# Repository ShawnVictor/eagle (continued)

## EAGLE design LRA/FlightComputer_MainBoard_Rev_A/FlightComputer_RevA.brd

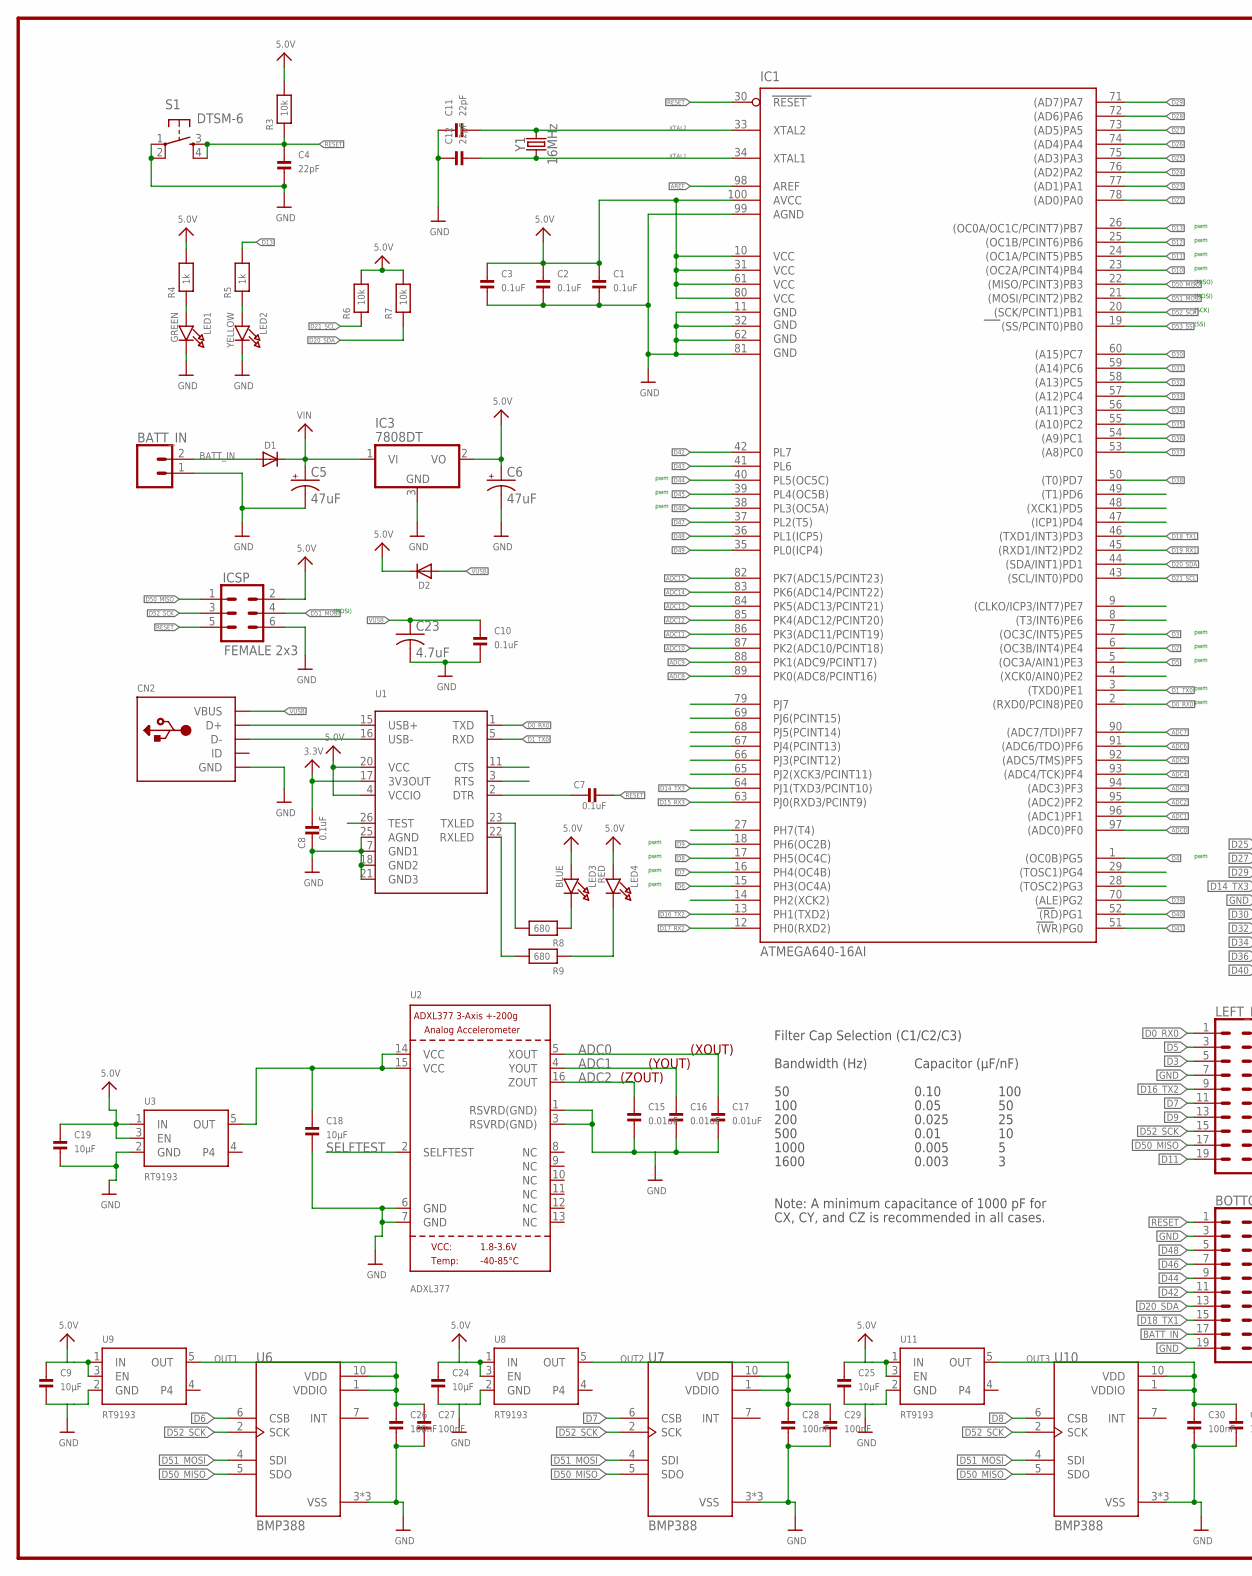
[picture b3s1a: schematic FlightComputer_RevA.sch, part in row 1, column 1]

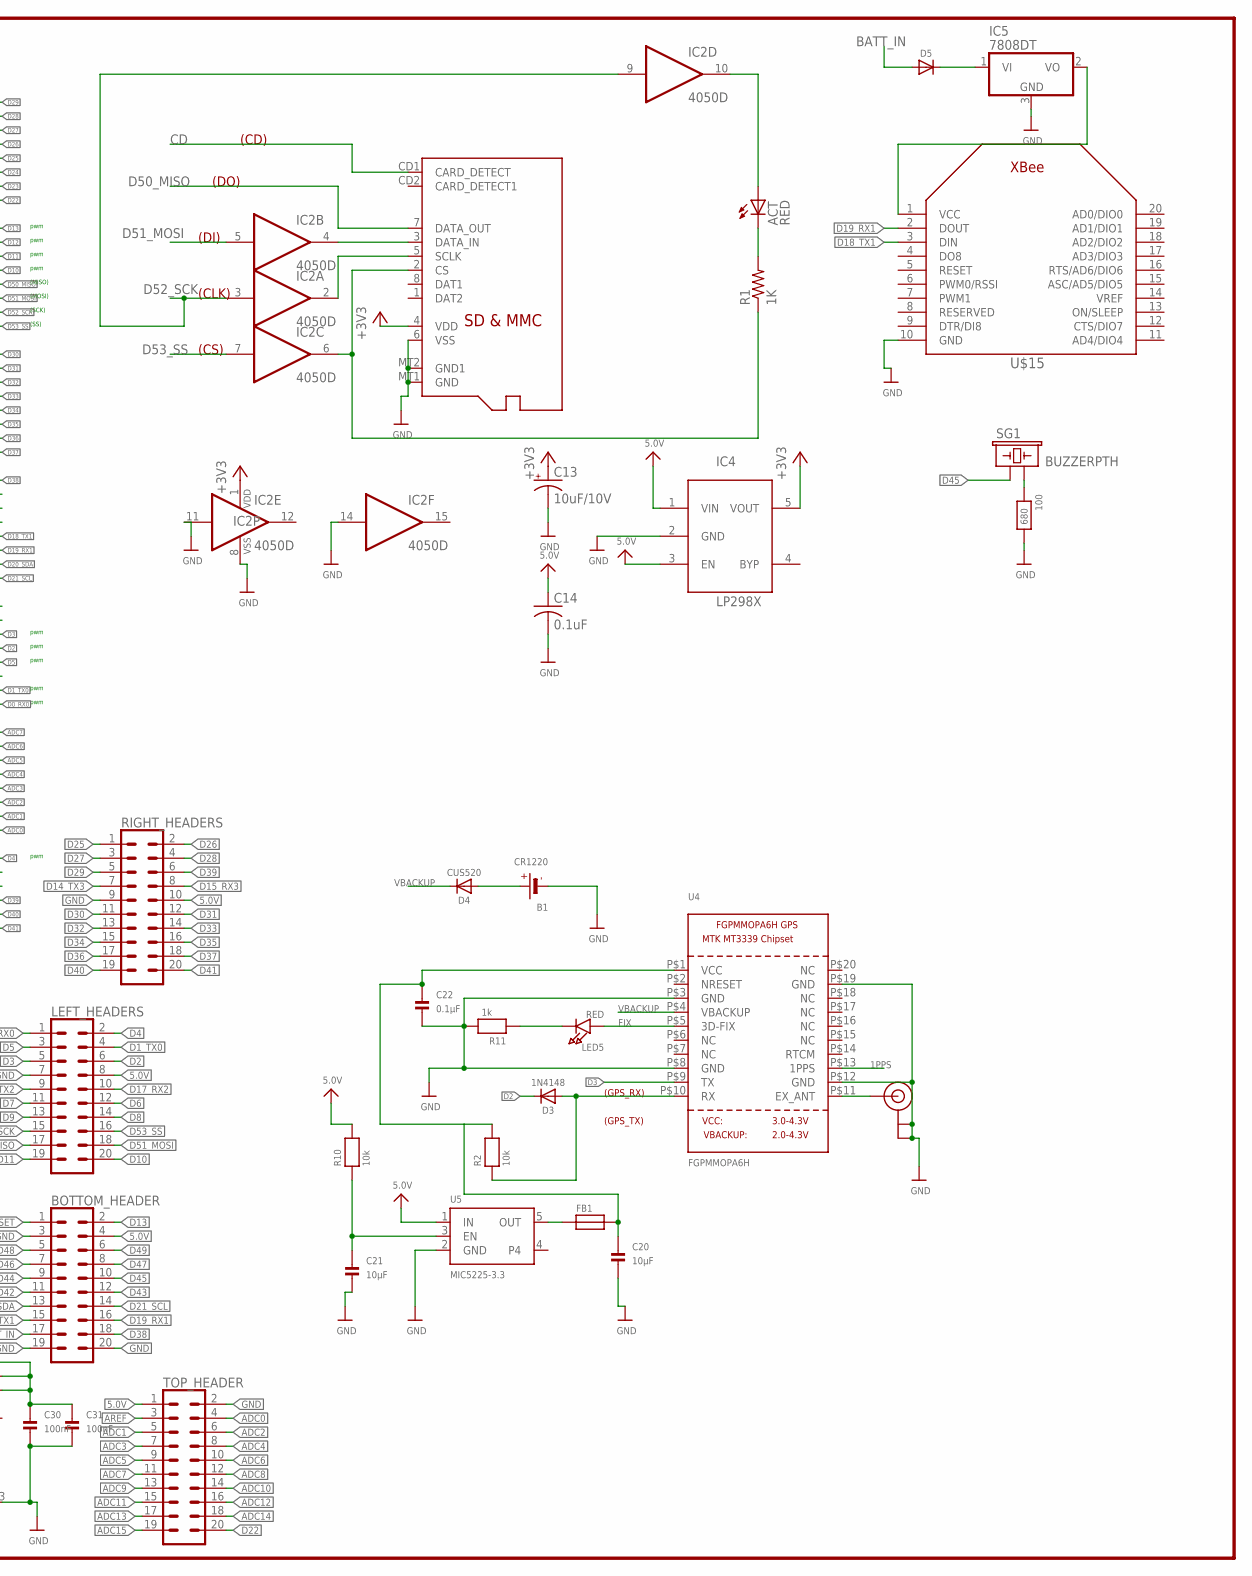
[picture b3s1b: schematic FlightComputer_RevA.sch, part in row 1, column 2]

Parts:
100: 680; 0603
ACT: RED; CHIP-LED0805
B1: CR1220
BATT_IN: CONN_02; 1X02
BOTTOM_HEADER: CONN_10X2; 2X10
C1, C2, C3, C7, C8, C10: 0.1uF; 0603
C4, C11, C12: 22pF; 0603
C5, C6: 47uF; PANASONIC_D
C9, C18, C19, C20, C21, C24, C25: 10µF; 0603
C13: 10uF/10V; A/3216-18R
C14: 0.1uF; C0805K
C15, C16, C17: 0.01uF; 0603
C22: 0.1µF; 0603
C23: 4.7uF; C0603
C26, C27, C28, C29, C30, C31: 100nF; 0603
CN2: USBMINIB; USB-MINIB
D1, D2, D5: DIODESOD-123; SOD-123
D3: 1N4148; SOD-323
D4: CUS520; SOD-323
FB1: FERRITE; 0603
IC1: ATMEGA640-16AI; TQFP100
IC2: 4050D; SO16
IC3, IC5: 7808DT; TO252
IC4: LP298XS; SOT23-5L
ICSP: FEMALE 2x3; 2X3
LED1: GREEN; CHIPLED_0603
LED2: YELLOW; CHIPLED_0603
LED3: BLUE; CHIPLED_0603
LED4: RED; CHIPLED_0603
LED5: RED; CHIPLED_0805
LEFT_HEADERS: CONN_10X2; 2X10
R1: 1K; R0805
R2, R3, R6, R7, R10: 10k; 0603
R4, R5, R11: 1k; 0603
R8, R9: 680; 0603
RIGHT_HEADERS: CONN_10X2; 2X10
S1: DTSM-6
SG1: BUZZERPTH; BUZZER-12MM
TOP_HEADER: CONN_10X2; 2X10
U1: FT232RLSSOP28; SSOP28DB
U2: ADXL377; LFCSP16_LQ
U3, U8, U9, U11: RT9193; SOT23-5
U4: FGPMMOPA6H
U5: MIC5225-3.3; SOT23-5
U6, U7, U10: BMP388; PQFN50P200X200X80-10N
U$15: XBEE
U$55: U.FL
X1: MICROSD
Y1: 16MHz; HC49US

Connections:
1PPS: U4.P$13 (1PPS)
3.3V: C8.2, U1.17 (3V3OUT)
5.0V: BOTTOM_HEADER.4, C1.1, C2.1, C3.1, C6.+, C9.1, C14.1, C19.1, C24.1, C25.1, D2.C, IC1.10 (VCC), IC1.31 (VCC1), IC1.61 (VCC2), IC1.80 (VCC3), IC1.100 (AVCC), IC3.2 (VO), IC4.1 (VIN), IC4.3 (EN), ICSP.2, LED3.A, LED4.A, LEFT_HEADERS.8, R3.2, R4.2, R6.2, R7.2, R10.2, RIGHT_HEADERS.10, TOP_HEADER.1, U1.4 (VCCIO), U1.20 (VCC), U3.1 (IN), U3.3 (EN), U5.1 (IN), U8.1 (IN), U8.3 (EN), U9.1 (IN), U9.3 (EN), U11.1 (IN), U11.3 (EN)
+3V3: C13.+, IC2.1 (VDD), IC4.5 (VOUT), X1.4 (VDD)
ADC0: C17.1, IC1.97 ((ADC0)PF0), TOP_HEADER.4, U2.5 (XOUT)
ADC1: C16.1, IC1.96 ((ADC1)PF1), TOP_HEADER.5, U2.4 (YOUT)
ADC2: C15.1, IC1.95 ((ADC2)PF2), TOP_HEADER.6, U2.16 (ZOUT)
ADC3: IC1.94 ((ADC3)PF3), TOP_HEADER.7
ADC4: IC1.93 ((ADC4/TCK)PF4), TOP_HEADER.8
ADC5: IC1.92 ((ADC5/TMS)PF5), TOP_HEADER.9
ADC6: IC1.91 ((ADC6/TDO)PF6), TOP_HEADER.10
ADC7: IC1.90 ((ADC7/TDI)PF7), TOP_HEADER.11
ADC8: IC1.89 (PK0(ADC8/PCINT16)), TOP_HEADER.12
ADC9: IC1.88 (PK1(ADC9/PCINT17)), TOP_HEADER.13
ADC10: IC1.87 (PK2(ADC10/PCINT18)), TOP_HEADER.14
ADC11: IC1.86 (PK3(ADC11/PCINT19)), TOP_HEADER.15
ADC12: IC1.85 (PK4(ADC12/PCINT20)), TOP_HEADER.16
ADC13: IC1.84 (PK5(ADC13/PCINT21)), TOP_HEADER.17
ADC14: IC1.83 (PK6(ADC14/PCINT22)), TOP_HEADER.18
ADC15: IC1.82 (PK7(ADC15/PCINT23)), TOP_HEADER.19
AREF: IC1.98 (AREF), TOP_HEADER.3
BATT_IN: BATT_IN.2, BOTTOM_HEADER.17, D1.A, D5.A
CD: X1.CD1 (CARD_DETECT)
D0_RX0: IC1.2 ((RXD0/PCIN8)PE0), LEFT_HEADERS.1, U1.1 (TXD)
D1_TX0: IC1.3 ((TXD0)PE1), LEFT_HEADERS.4, U1.5 (RXD)
D2: D3.C, IC1.6 ((OC3B/INT4)PE4), LEFT_HEADERS.6
D3: IC1.7 ((OC3C/INT5)PE5), LEFT_HEADERS.5, U4.P$9 (TX)
D4: IC1.1 ((OC0B)PG5), LEFT_HEADERS.2
D5: IC1.5 ((OC3A/AIN1)PE3), LEFT_HEADERS.3
D6: IC1.15 (PH3(OC4A)), LEFT_HEADERS.12, U6.6 (CSB)
D7: IC1.16 (PH4(OC4B)), LEFT_HEADERS.11, U7.6 (CSB)
D8: IC1.17 (PH5(OC4C)), LEFT_HEADERS.14, U10.6 (CSB)
D9: IC1.18 (PH6(OC2B)), LEFT_HEADERS.13
D10: IC1.23 ((OC2A/PCINT4)PB4), LEFT_HEADERS.20
D11: IC1.24 ((OC1A/PCINT5)PB5), LEFT_HEADERS.19
D12: IC1.25 ((OC1B/PCINT6)PB6)
D13: BOTTOM_HEADER.2, IC1.26 ((OC0A/OC1C/PCINT7)PB7), R5.2
D14_TX3: IC1.64 (PJ1(TXD3/PCINT10)), RIGHT_HEADERS.7
D15_RX3: IC1.63 (PJ0(RXD3/PCINT9)), RIGHT_HEADERS.8
D16_TX2: IC1.13 (PH1(TXD2)), LEFT_HEADERS.9
D17_RX2: IC1.12 (PH0(RXD2)), LEFT_HEADERS.10
D18_TX1: BOTTOM_HEADER.15, IC1.46 ((TXD1/INT3)PD3), U$15.3 (DIN)
D19_RX1: BOTTOM_HEADER.16, IC1.45 ((RXD1/INT2)PD2), U$15.2 (DOUT)
D20_SDA: BOTTOM_HEADER.13, IC1.44 ((SDA/INT1)PD1), R7.1
D21_SCL: BOTTOM_HEADER.14, IC1.43 ((SCL/INT0)PD0), R6.1
D22: IC1.78 ((AD0)PA0), TOP_HEADER.20
D23: IC1.77 ((AD1)PA1)
D24: IC1.76 ((AD2)PA2)
D25: IC1.75 ((AD3)PA3), RIGHT_HEADERS.1
D26: IC1.74 ((AD4)PA4), RIGHT_HEADERS.2
D27: IC1.73 ((AD5)PA5), RIGHT_HEADERS.3
D28: IC1.72 ((AD6)PA6), RIGHT_HEADERS.4
D29: IC1.71 ((AD7)PA7), RIGHT_HEADERS.5
D30: IC1.60 ((A15)PC7), RIGHT_HEADERS.11
D31: IC1.59 ((A14)PC6), RIGHT_HEADERS.12
D32: IC1.58 ((A13)PC5), RIGHT_HEADERS.13
D33: IC1.57 ((A12)PC4), RIGHT_HEADERS.14
D34: IC1.56 ((A11)PC3), RIGHT_HEADERS.15
D35: IC1.55 ((A10)PC2), RIGHT_HEADERS.16
D36: IC1.54 ((A9)PC1), RIGHT_HEADERS.17
D37: IC1.53 ((A8)PC0), RIGHT_HEADERS.18
D38: BOTTOM_HEADER.18, IC1.50 ((T0)PD7)
D39: IC1.70 ((ALE)PG2), RIGHT_HEADERS.6
D40: IC1.52 ((RD)PG1), RIGHT_HEADERS.19
D41: IC1.51 ((WR)PG0), RIGHT_HEADERS.20
D42: BOTTOM_HEADER.11, IC1.42 (PL7)
D43: BOTTOM_HEADER.12, IC1.41 (PL6)
D44: BOTTOM_HEADER.9, IC1.40 (PL5(OC5C))
D45: BOTTOM_HEADER.10, IC1.39 (PL4(OC5B)), SG1.+ (1)
D46: BOTTOM_HEADER.7, IC1.38 (PL3(OC5A))
D47: BOTTOM_HEADER.8, IC1.37 (PL2(T5))
D48: BOTTOM_HEADER.5, IC1.36 (PL1(ICP5))
D49: BOTTOM_HEADER.6, IC1.35 (PL0(ICP4))
D50_MISO: IC1.22 ((MISO/PCINT3)PB3), ICSP.1, LEFT_HEADERS.17, U6.5 (SDO), U7.5 (SDO), U10.5 (SDO), X1.7 (DATA_OUT)
D51_MOSI: IC1.21 ((MOSI/PCINT2)PB2), IC2.5 (I), ICSP.4, LEFT_HEADERS.18, U6.4 (SDI), U7.4 (SDI), U10.4 (SDI)
D52_SCK: IC1.20 ((SCK/PCINT1)PB1), IC2.3 (I), IC2.9 (I), ICSP.3, LEFT_HEADERS.15, U6.2 (SCK), U7.2 (SCK), U10.2 (SCK)
D53_SS: IC1.19 ((SS/PCINT0)PB0), IC2.7 (I), LEFT_HEADERS.16
FIX: LED5.A, U4.P$5 (3D-FIX)
GND: 100.2, B1.-, BATT_IN.1, BOTTOM_HEADER.3, BOTTOM_HEADER.19, BOTTOM_HEADER.20, C1.2, C2.2, C3.2, C4.2, C5.-, C6.-, C8.1, C9.2, C10.1, C11.1, C12.1, C13.-, C14.2, C15.2, C16.2, C17.2, C18.2, C19.2, C20.2, C21.2, C22.2, C23.2, C24.2, C25.2, C26.2, C27.2, C28.2, C29.2, C30.2, C31.2, CN2.GND, IC1.11 (GND), IC1.32 (GND1), IC1.62 (GND2), IC1.81 (GND3), IC1.99 (AGND), IC2.8 (VSS), IC2.11 (I), IC2.14 (I), IC3.3 (GND), IC4.2 (GND), IC5.3 (GND), ICSP.6, LED1.C, LED2.C, LEFT_HEADERS.7, R11.2, RIGHT_HEADERS.9, S1.1, S1.2, TOP_HEADER.2, U1.7 (GND1), U1.18 (GND2), U1.21 (GND3), U1.25 (AGND), U2.1 (RSVRD(GND)), U2.3 (RSVRD(GND)), U2.6 (GND), U2.7 (GND), U3.2 (GND), U4.P$3 (GND), U4.P$8 (GND), U4.P$12 (GND), U4.P$19 (GND), U5.2 (GND), U6.3 (VSS), U6.8 (VSS), U6.9 (VSS), U7.3 (VSS), U7.8 (VSS), U7.9 (VSS), U8.2 (GND), U9.2 (GND), U10.3 (VSS), U10.8 (VSS), U10.9 (VSS), U11.2 (GND), U$15.10 (GND), U$55.P$1 (GND), U$55.P$2 (GND), X1.6 (VSS), X1.MT1 (GND), X1.MT2 (GND1)
unnamed: ACT.A, IC2.10 (O)
unnamed: D5.C, IC5.1 (VI)
unnamed: CN2.D+, U1.15 (USB+)
unnamed: CN2.D-, U1.16 (USB-)
unnamed: LED1.A, R4.1
unnamed: LED2.A, R5.1
unnamed: LED3.C, R8.1
unnamed: R9.2, U1.22 (RXLED)
unnamed: R8.2, U1.23 (TXLED)
unnamed: LED4.C, R9.1
unnamed: IC2.2 (O), X1.5 (SCLK)
unnamed: C7.1, U1.2 (DTR)
unnamed: IC2.6 (O), R1.1, X1.2 (CS)
unnamed: ACT.C, R1.2
unnamed: IC2.4 (O), X1.3 (DATA_IN)
unnamed: U4.P$11 (EX_ANT), U$55.P$3 (SIGNAL)
unnamed: C18.1, U2.14 (VCC), U2.15 (VCC), U3.5 (OUT)
unnamed: C21.1, R10.1, U5.3 (EN)
unnamed: D3.A, R2.1, U4.P$10 (RX)
unnamed: B1.+$1 (+), B1.+$2 (+), D4.A
unnamed: C20.1, C22.1, FB1.2, R2.2, U4.P$1 (VCC)
unnamed: 100.1, SG1.- (2)
unnamed: LED5.C, R11.1
OUT: FB1.1, U5.5 (OUT)
OUT1: C26.1, C27.1, U6.1 (VDDIO), U6.10 (VDD), U9.5 (OUT)
OUT2: C28.1, C29.1, U7.1 (VDDIO), U7.10 (VDD), U8.5 (OUT)
OUT3: C30.1, C31.1, U10.1 (VDDIO), U10.10 (VDD), U11.5 (OUT)
RESET: BOTTOM_HEADER.1, C4.1, C7.2, IC1.30 (RESET), ICSP.5, R3.1, S1.3, S1.4
SELFTEST: U2.2 (SELFTEST)
VBACKUP: D4.C, U4.P$4 (VBACKUP)
VCC: IC5.2 (VO), U$15.1 (VCC)
VIN: C5.+, D1.C, IC3.1 (VI)
VUSB: C10.2, C23.1, CN2.VBUS, D2.A
XTAL1: C12.2, IC1.34 (XTAL1), Y1.1
XTAL2: C11.2, IC1.33 (XTAL2), Y1.2

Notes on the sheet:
pwm
(SS)
(SCK)
(MOSI)
(MISO)
(CD)
(DO)
(DI)
(CLK)
(CS)
Filter Cap Selection (C1/C2/C3)
Bandwidth (Hz)
Capacitor (µF/nF)
100
200
500
1000
1600
0.10
0.05
0.025
0.01
0.005
0.003
Note: A minimum capacitance of 1000 pF for
CX, CY, and CZ is recommended in all cases.
(XOUT)
(YOUT)
(ZOUT)
(GPS_RX)
(GPS_TX)

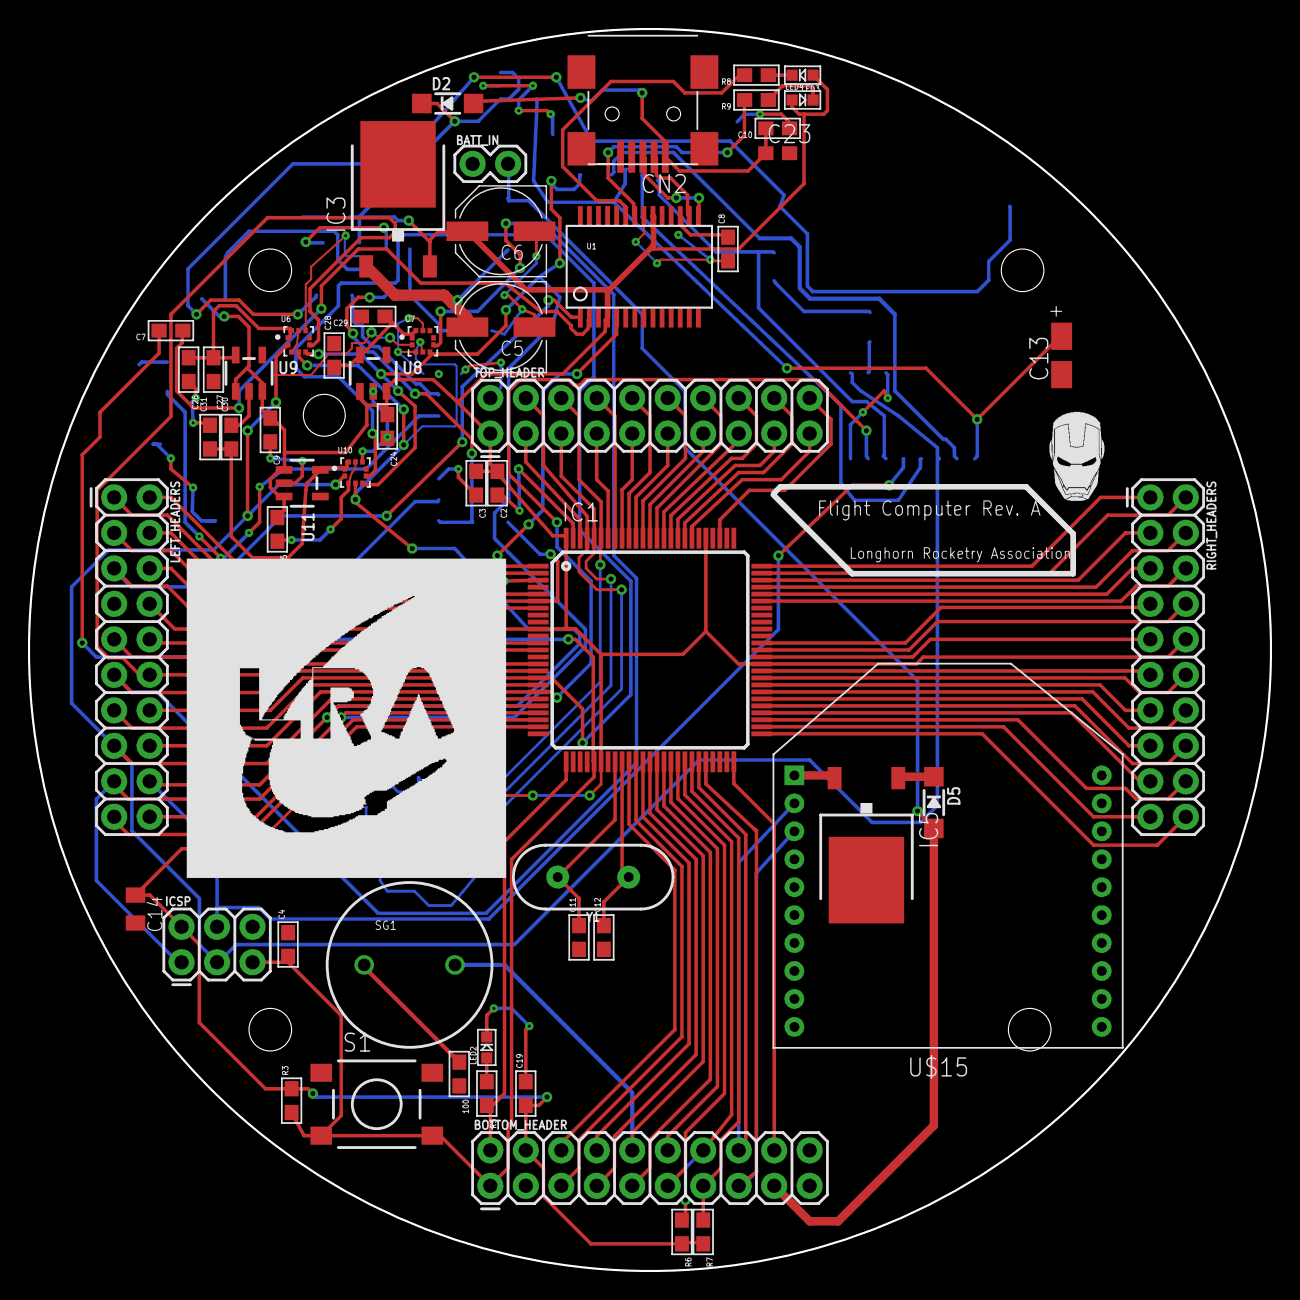
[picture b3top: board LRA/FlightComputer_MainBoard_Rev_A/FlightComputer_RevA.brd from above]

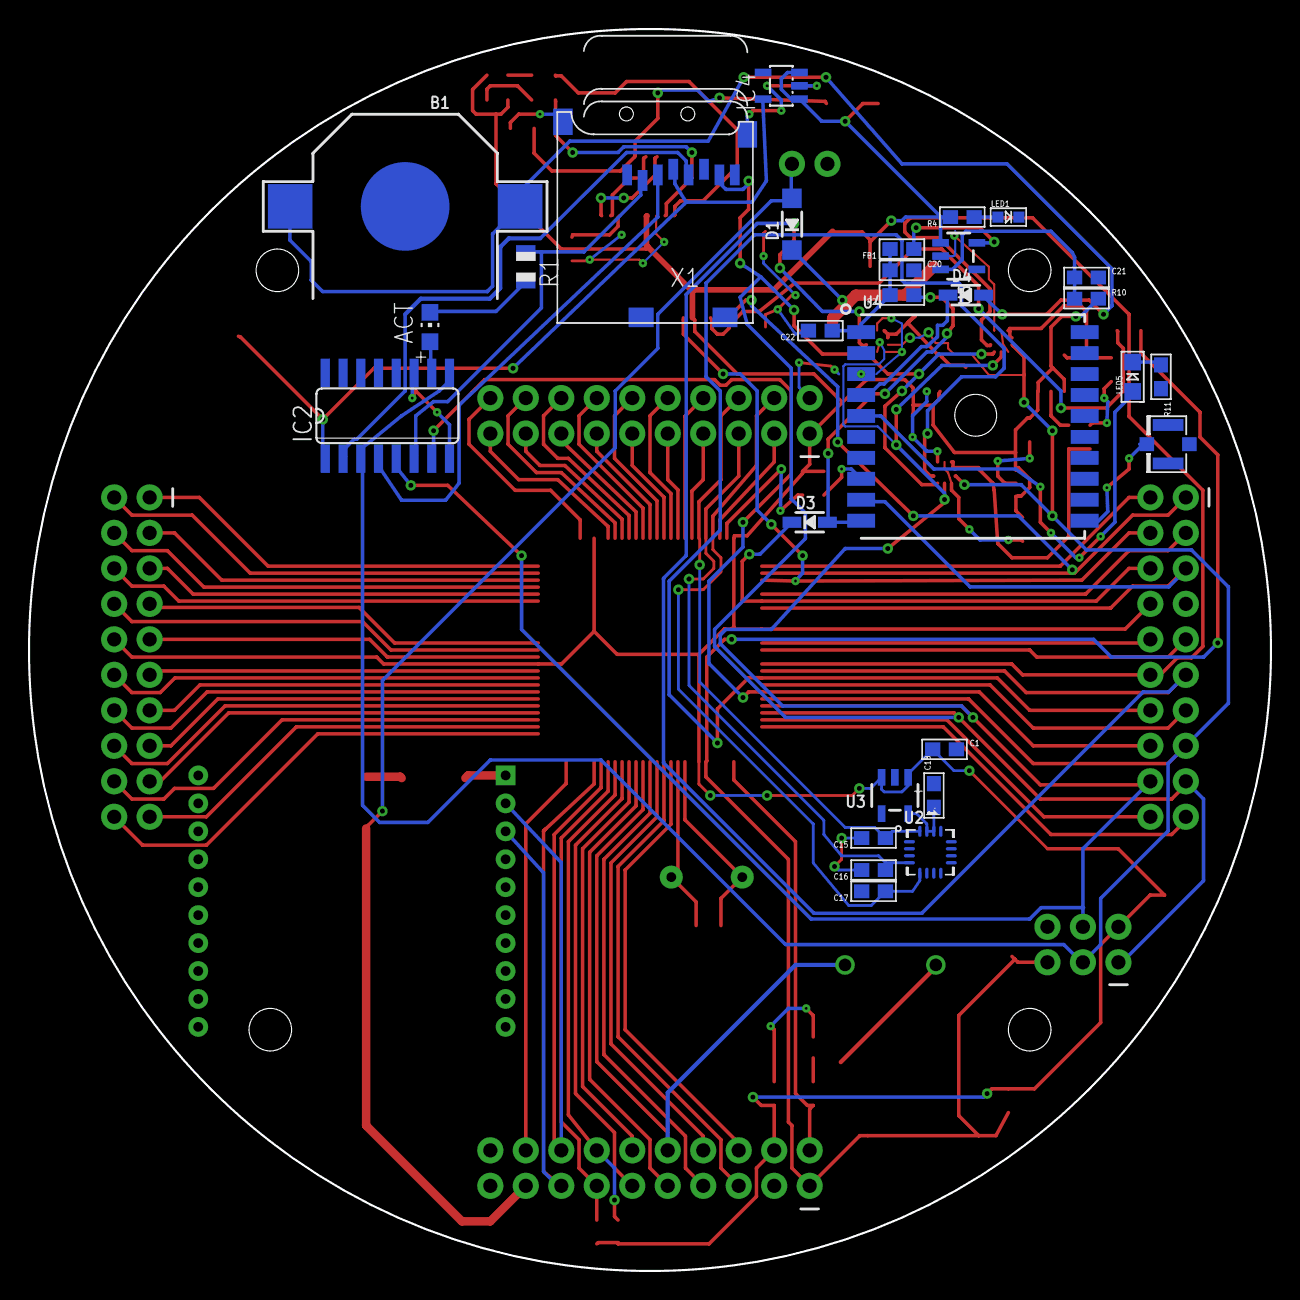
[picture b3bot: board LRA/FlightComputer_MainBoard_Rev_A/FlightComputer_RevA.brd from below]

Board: 2 copper layers, 88.9 x 88.9 mm, 85 parts (29 on the bottom side), 108 nets.
